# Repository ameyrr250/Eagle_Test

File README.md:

# Eagle_Test
Test Repository for eagle
v1.0-Checking if public access works.
=======
Added bitbucket

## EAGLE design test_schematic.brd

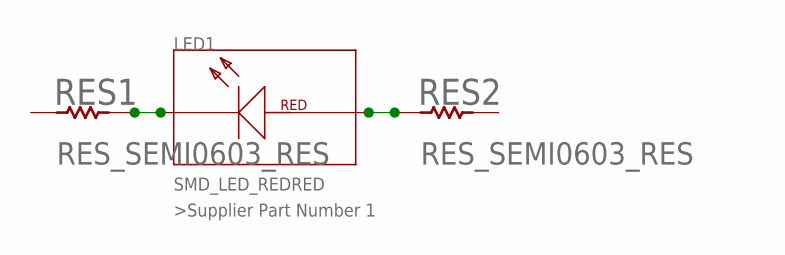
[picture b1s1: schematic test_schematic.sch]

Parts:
LED1: SMD_LED_REDRED; 0603_LED_RED
RES1, RES2: RES_SEMI0603_RES; 0603_RESISTOR

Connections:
unnamed: LED1.1 (K), RES1.2
unnamed: LED1.2 (A), RES2.1

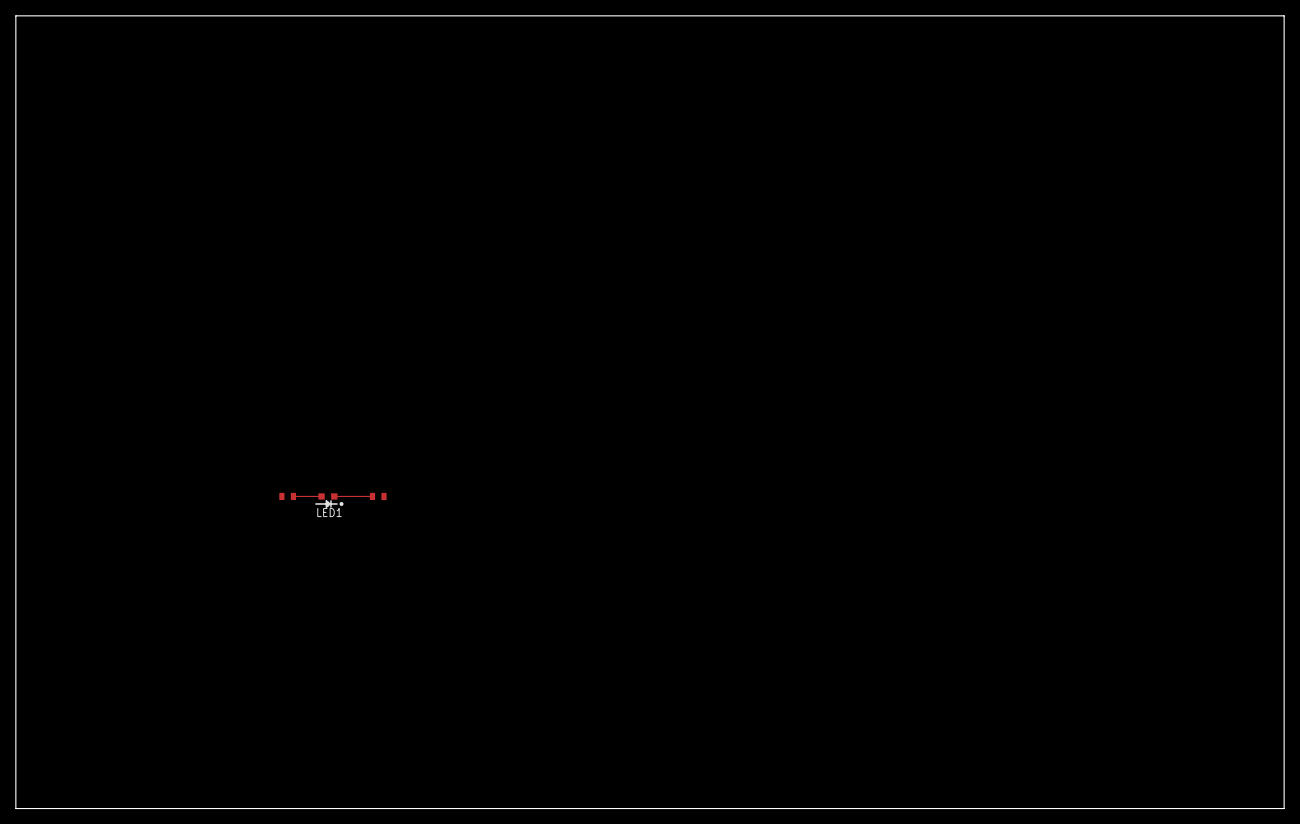
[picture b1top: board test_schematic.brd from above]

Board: 2 copper layers, 160.0 x 100.0 mm, 3 parts (0 on the bottom side), 2 nets.

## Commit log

2020-04-06 Testing the eagle library use
2020-04-06 check public 2.0
2020-04-06 adding to bitbucket
